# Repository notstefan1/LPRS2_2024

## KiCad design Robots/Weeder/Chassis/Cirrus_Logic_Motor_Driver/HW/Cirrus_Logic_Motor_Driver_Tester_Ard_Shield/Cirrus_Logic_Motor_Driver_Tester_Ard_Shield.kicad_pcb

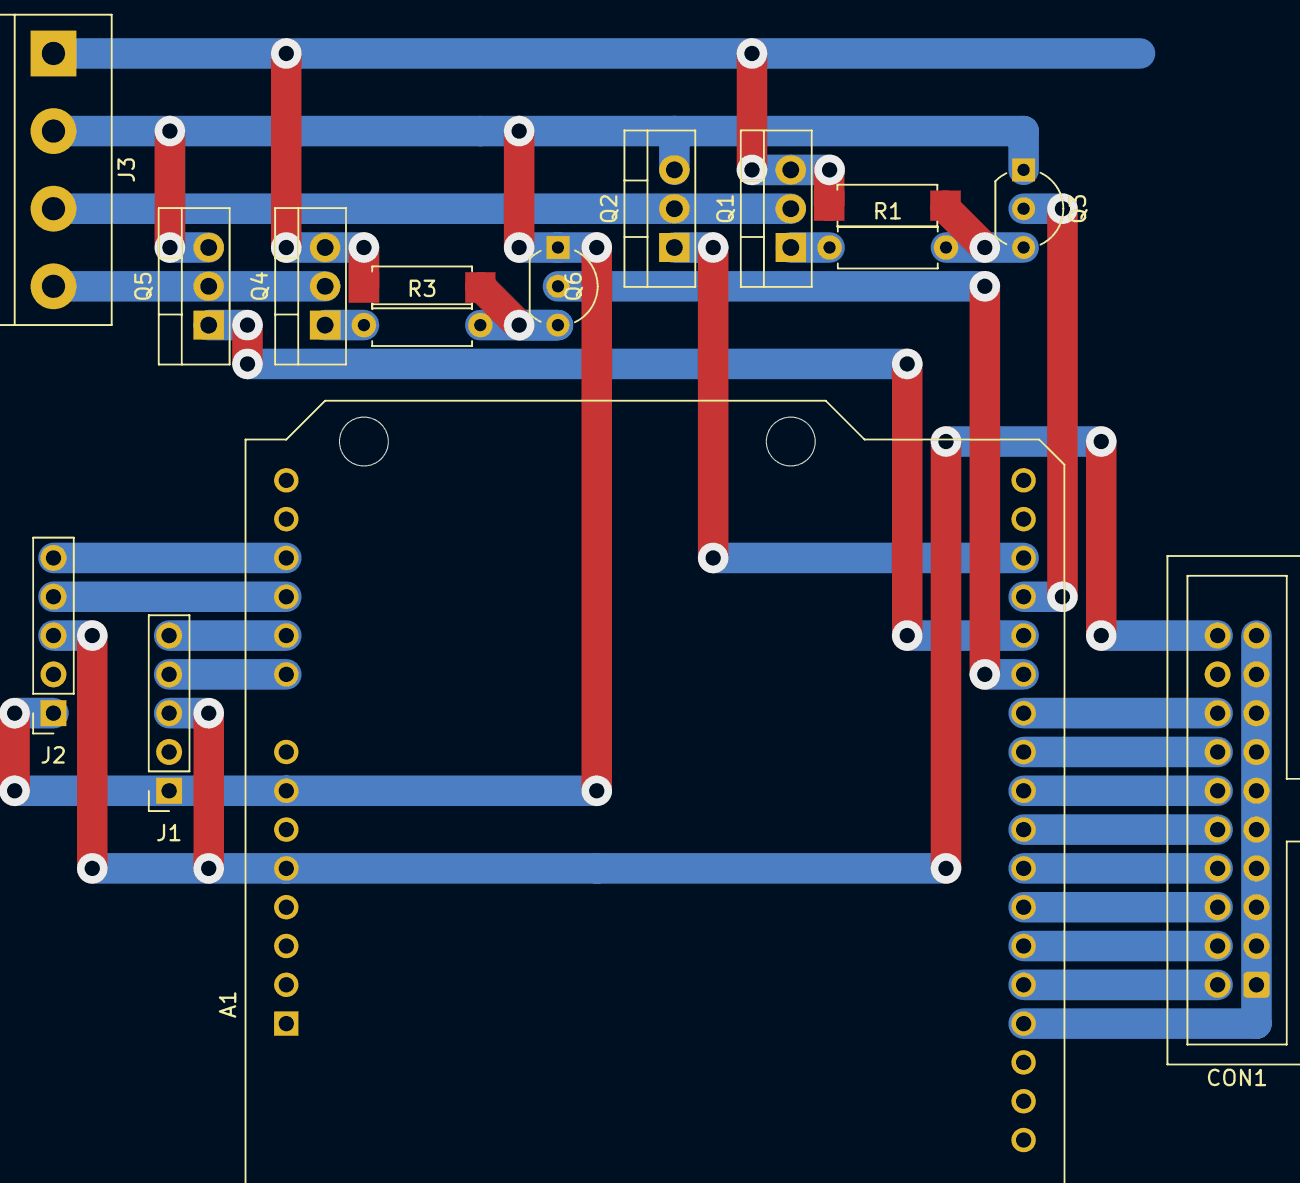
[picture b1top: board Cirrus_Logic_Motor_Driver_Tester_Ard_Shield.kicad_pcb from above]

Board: 2 copper layers, 15 parts (0 on the bottom side), 26 nets.

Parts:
A1: Arduino_UNO_R2; Arduino_UNO_R3_WithMountingHoles_Snapped_to_P2.54mm
CON1: 2x10 2.54mm male IDC header; IDC-Header_2x10_P2.54mm_Vertical
J1, J2: 1x5 2.54mm female; PinSocket_1x05_P2.54mm_Vertical
J3: Screw_Terminal_01x04; TerminalBlock_bornier-4_P5.08mm
Q1, Q4: IRF9Z34N; TO-220-3_Vertical
Q2, Q5: IRLZ34N; TO-220-3_Vertical
Q3, Q6: 2N7000; TO-92_Inline_Wide
R1, R3: 220; R_Axial_DIN0207_L6.3mm_D2.5mm_P7.62mm_Horizontal
R2, R4: 470; R_Axial_DIN0207_L6.3mm_D2.5mm_Pinf_Horizontal

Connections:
+5V: A1.5 (+5V), CON1.20, J1.3, J2.3
+24V: J3.1, Q1.3 (S), Q4.3 (S), R2.1, R4.1
/A0: A1.9 (A0), J1.4
/A1: A1.11 (A2), J2.4
/B0: A1.10 (A1), J1.5
/B1: A1.12 (A3), J2.5
/FAULT: A1.21 (D6), CON1.16
/UH: A1.28 (D13), CON1.2
/UL: A1.27 (D12), CON1.4
/U_COLD: J3.3, Q1.2 (D), Q2.2 (D)
/U_SSD_H: A1.18 (D3), Q3.2 (G)
/U_SSD_L: A1.17 (D2), Q2.1 (G)
/VH: A1.26 (D11), CON1.6
/VL: A1.25 (D10), CON1.8
/V_COLD: J3.4, Q4.2 (D), Q5.2 (D)
/V_SSD_H: A1.20 (D5), Q6.2 (G)
/V_SSD_L: A1.19 (D4), Q5.1 (G)
/WH: A1.24 (D9), CON1.10
/WL: A1.23 (D8), CON1.12
/~EN: A1.22 (D7), CON1.14
GND: A1.7 (GND), J1.1, J2.1, J3.2, Q2.3 (S), Q3.1 (S), Q5.3 (S), Q6.1 (S)
GND1: A1.29 (GND), CON1.1, CON1.3, CON1.5, CON1.7, CON1.9, CON1.11, CON1.13, CON1.15, CON1.17, CON1.19
unnamed: Q1.1 (G), R1.1
unnamed: Q3.3 (D), R1.2, R2.2
unnamed: Q4.1 (G), R3.1
unnamed: Q6.3 (D), R3.2, R4.2

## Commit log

2024-05-24 Shield for chassis.
2024-05-24 Moved.
2024-05-24 Possible solution for VFD.
2024-05-26 Engine.
2024-05-27 Old waf distclean way.
2024-05-27 Src.
2024-05-29 Correction.
2024-06-11 added encoder code
2024-06-11 pcb done
2024-06-14 add mising files
2024-06-18 fixed driver code
2024-06-18 prettied up code
2024-06-20 added Docs and rpm counter
